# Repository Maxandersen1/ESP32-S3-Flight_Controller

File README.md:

# ESP32-S3 Custom Flight Controller

A custom-designed drone flight controller built from the ground up around the ESP32-S3 microcontroller. This project is a work-in-progress, covering everything from custom PCB design in KiCad to low-level sensor drivers and Web Serial 3D visualization.

## Hardware Features
- **Microcontroller**: ESP32-S3-WROOM-1 (Dual-Core Xtensa LX7, 240MHz)
- **IMU**: Bosch BMI088 (6-axis accelerometer & gyroscope) via SPI
- **Barometer**: Bosch BMP388 via I2C
- **Power System**: Onboard TPS54331 buck converter (battery Vin to 5V) & AMS1117-3.3 LDO
- **PCB**: Custom 4-layer PCB designed in KiCad, hand-soldered SMD components.

## Assembled PCB

## Hardware Design Process

### 1. Schematic
The schematic was designed in KiCad and ordered as a 4-layer PCB from JLCPCB.

### 2. PCB Layout & Stackup
The layout was routed in KiCad with the following dedicated 4-layer stackup:
* **Layer 1 – Top Layer (F.Cu):** Primary signal layer used for component placement (ESP32-S3, IMU, Barometer) and high-speed SPI/I2C trace routing.
* **Layer 2 – Inner Layer 1 (In1.Cu):** Dedicated internal Ground Plane (GND) providing low-impedance return paths and EMI shielding for sensitive sensors.
* **Layer 3 – Inner Layer 2 (In2.Cu):** Dedicated Power Plane with split power zones distributing clean 3.3V and 5V power across the board.
* **Layer 4 – Bottom Layer (B.Cu):** Secondary signal and ground layer used for remaining routing and bottom-side thermal dissipation.

## Bill of Materials (BOM)

### Integrated Circuits & Active Components
| Designator | Component / Part | Package | Qty | Function |
| :--- | :--- | :--- | :--- | :--- |
| **U1** | ESP32-S3-WROOM-1 | SMD Module | 1 | Main Flight Controller MCU |
| **U3** | Bosch BMI088 | LGA-16 | 1 | 6-Axis IMU (SPI) |
| **U4** | Bosch BMP388 | LGA-10 | 1 | Barometric Pressure & Altitude Sensor (I2C) |
| **U5** | TI TPS54331DG4 | SOIC-8 | 1 | Step-Down Buck Converter (Battery Vin to 5V) |
| **U6** | AMS1117-3.3 | SOT-223 | 1 | Low-Dropout (LDO) Linear Voltage Regulator (3.3V) |
| **U2** | USBLC6-2SC6 | SOT-23-6 | 1 | Low-Capacitance ESD Protection Array (USB) |
| **D1, D2, D3** | SS14 / SS34 | SMA (DO-214AC) | 3 | Schottky Barrier Diodes |
| **L1** | 15 µH (e.g. LVS606020) | SMD (~6x6 mm) | 1 | Power Inductor for Buck Converter |

### Connectors & Switches
| Designator | Description | Qty | Function |
| :--- | :--- | :--- | :--- |
| **J1** | USB-C 12-pin (TYPE-C-31-M-12) | 1 | USB Data / Programming & 5V Power |
| **J3** | JST-SH 8-Pin SMD (SM08B-SRSS-TB) | 1 | 4-in-1 ESC Interconnect (PWM / DSHOT signals) |
| **J2, J4** | 2.54mm Pitch Pin Headers | 2 | RC Receiver (UART) & Expansion / Debug pins |
| **SW1, SW2** | SMD Tactile Push Buttons | 2 | Bootloader & Hardware Reset |

### Passives Summary
* **Capacitors:**
  * `100 nF (0603)` — **8 pcs** (Decoupling for MCU, sensors, and regulators)
  * `10 nF (0603)` — **2 pcs** (Noise filtering / compensation)
  * `3.3 nF (0603)` — **1 pc** (Buck converter compensation loop)
  * `4.7 µF (0603)` — **1 pc** (Bulk decoupling)
  * `10 µF (0805)` — **1 pc** (LDO input/output stabilization)
  * `22 µF (0805)` — **4 pcs** (High-capacitance power rail smoothing)
* **Resistors (all 0603):**
  * `10 kΩ` — **7 pcs** (Pull-ups & boot mode configuration)
  * `4.7 kΩ` — **2 pcs** (I2C bus pull-ups for SDA / SCL)
  * `5.1 kΩ` — **2 pcs** (USB-C CC line pull-downs for 5V power negotiation)
  * `100 kΩ` — **2 pcs** (Voltage dividers & enable lines)
  * `30 kΩ` — **1 pc** (Feedback network)
  * `52.3 kΩ` — **1 pc** (High-precision feedback resistor for buck regulator)

## Software / Firmware
The firmware is written in C++ (Arduino framework) and features:
- **Raw SPI Communication**: Bypasses bloated libraries to communicate directly with the BMI088 registers, resolving complex ESP32 HAL macro conflicts.
- **Sensor Fusion**: Implements a custom Complementary Filter combining high-speed gyro data with accelerometer gravity vectors for stable, drift-free Pitch and Roll calculation.
- **Barometric Altimeter**: Features an auto-zeroing routine on startup to establish local ground-level pressure before calculating relative altitude in meters.

## 3D Web Visualizer
Included in the `tools/` directory is a custom HTML5/Three.js 3D drone visualizer. 
It uses the modern **Web Serial API** to connect directly to the flight controller via USB (no servers required) and renders the drone's orientation in real-time at 60fps based on the live IMU telemetry.

## Directory Structure
- `hardware/`: KiCad schematics and PCB layout files.
- `firmware/FlightController/`: The main C++ Arduino sketch containing sensor drivers and mathematical filters.
- `tools/`: Contains `3D_Viewer.html` (Double-click to open in a modern browser).

## Roadmap / To-Do
- [x] PCB Design & Assembly
- [x] I2C & SPI Bring-up
- [x] Raw IMU & Barometer Data Extraction
- [x] Sensor Fusion (Complementary Filter)
- [x] Real-time 3D Visualization
- [ ] PID Controller Implementation
- [ ] ESC Motor Output (DSHOT/PWM)
- [ ] Radio Receiver Integration (ExpressLRS/Crossfire)

*Hardware designed from scratch by Max. Firmware and 3D visualization developed using AI-assisted pair programming.*

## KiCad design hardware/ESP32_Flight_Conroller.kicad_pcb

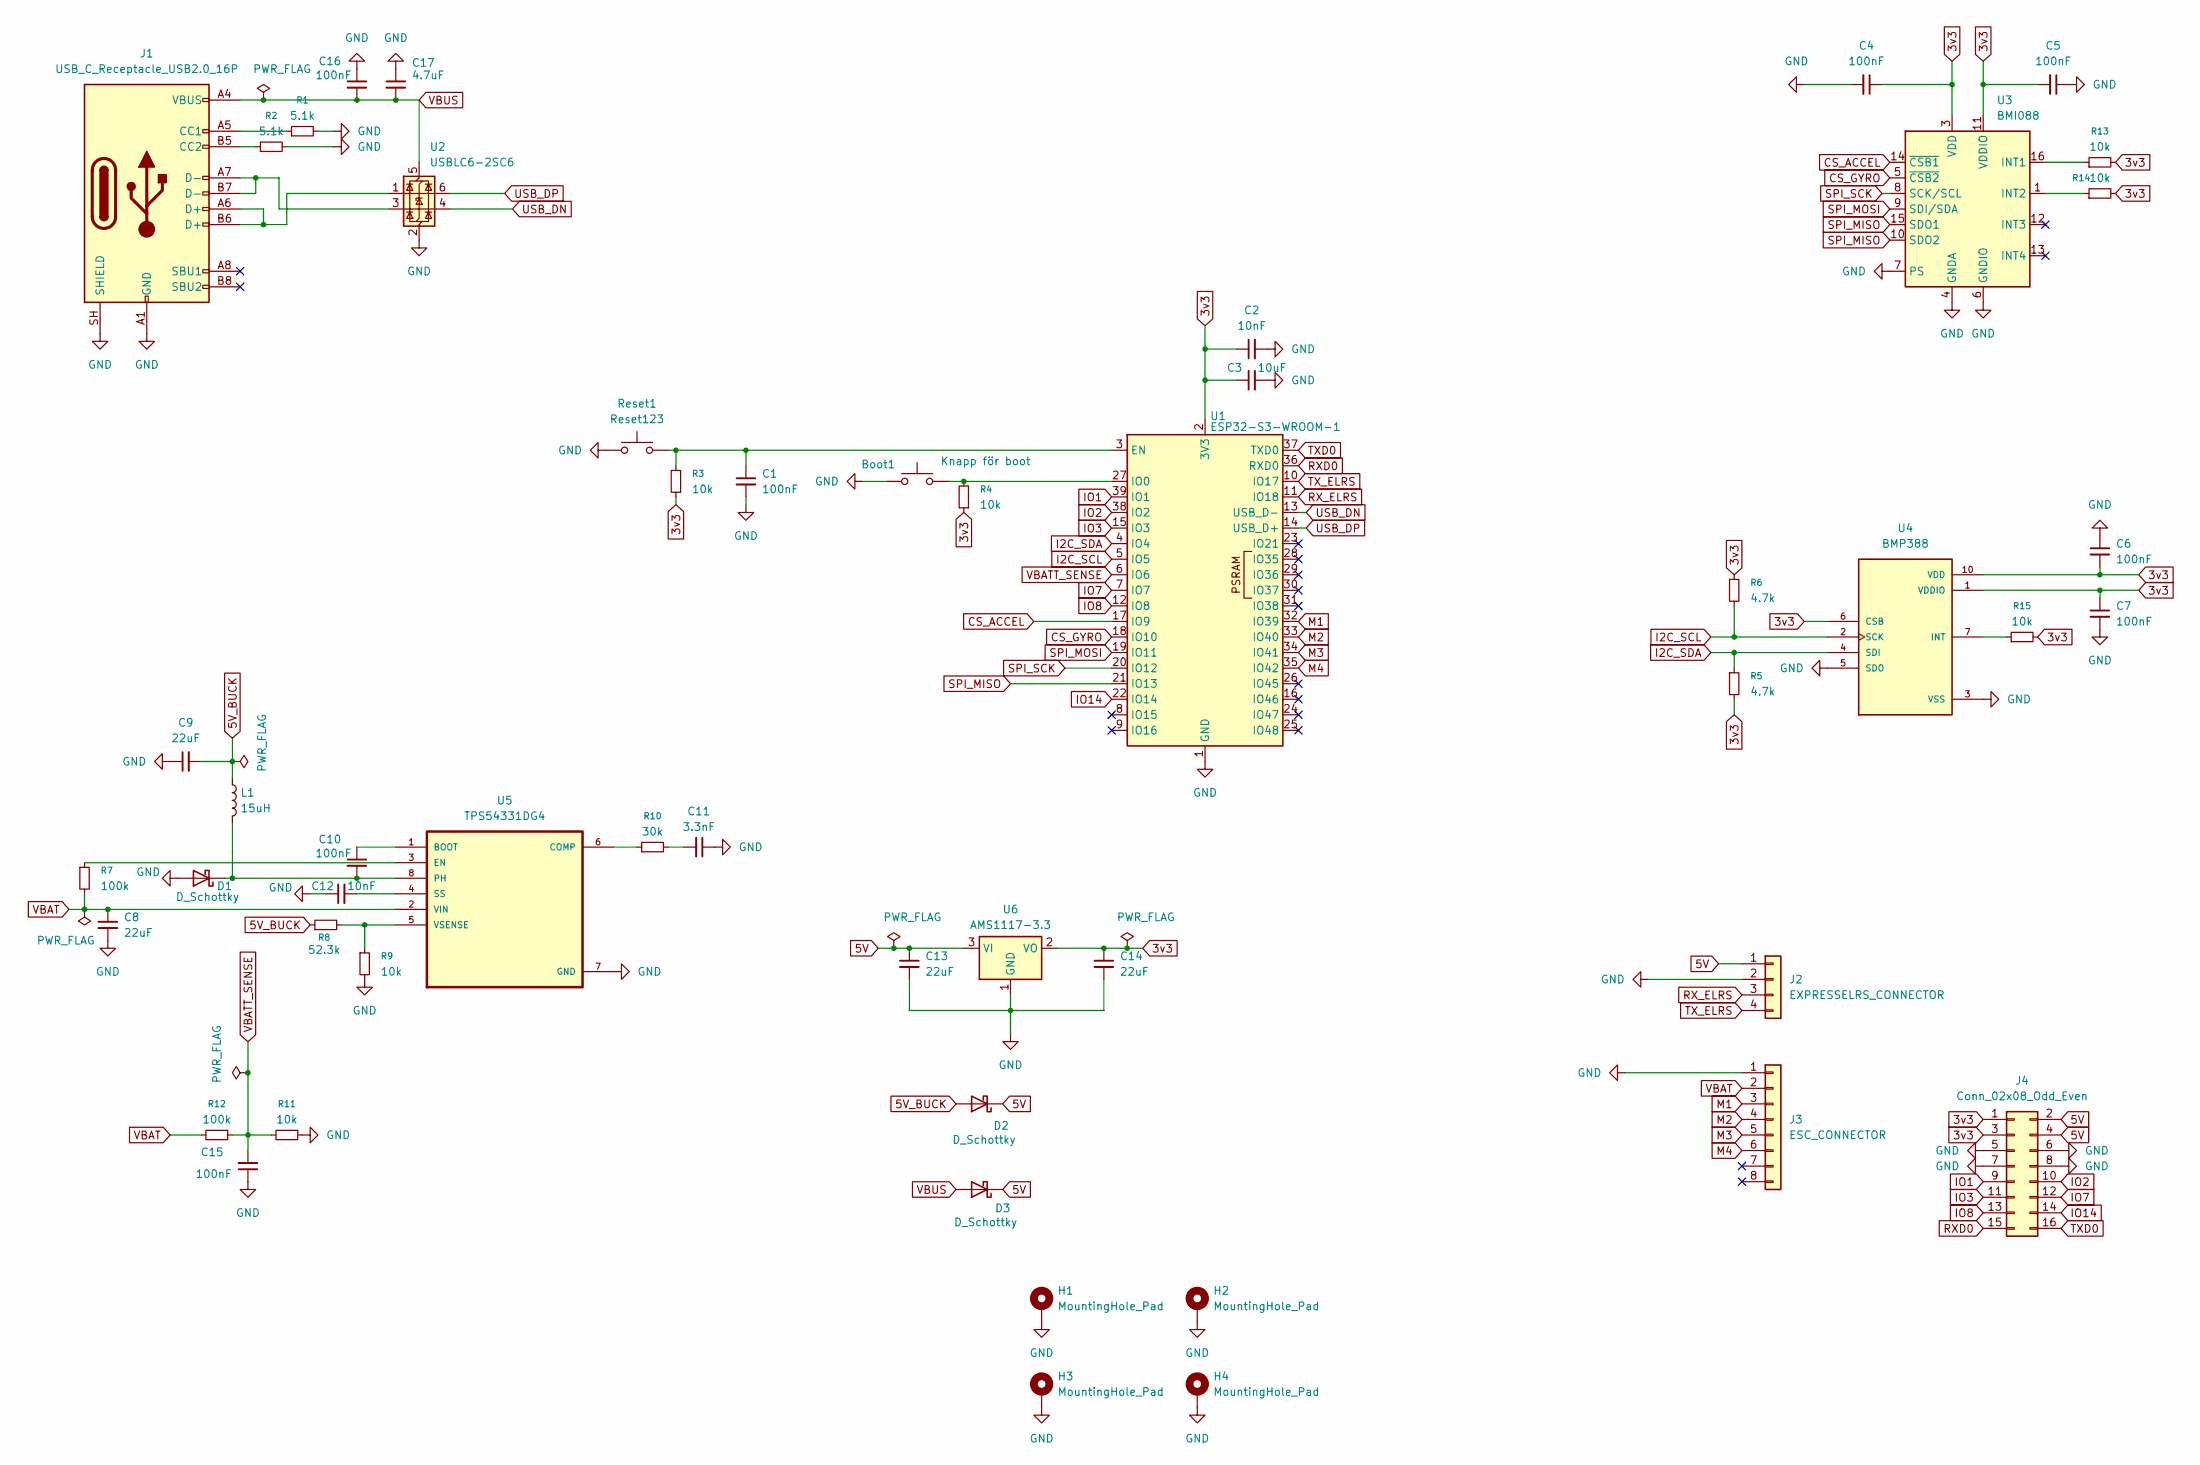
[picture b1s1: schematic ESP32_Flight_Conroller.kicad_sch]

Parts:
Boot1: Knapp för boot; SW_SPST_B3U-1000P
C1, C4, C5, C6, C7, C10, C15, C16: 100nF; C_0603_1608Metric_Pad1.08x0.95mm_HandSolder
C2, C12: 10nF; C_0603_1608Metric_Pad1.08x0.95mm_HandSolder
C3: 10uF; C_0805_2012Metric_Pad1.18x1.45mm_HandSolder
C8, C9, C13, C14: 22uF; C_0805_2012Metric_Pad1.18x1.45mm_HandSolder
C11: 3.3nF; C_0603_1608Metric_Pad1.08x0.95mm_HandSolder
C17: 4.7uF; C_0603_1608Metric_Pad1.08x0.95mm_HandSolder
D1, D2, D3: D_Schottky; D_SMA
H1, H2, H3, H4: MountingHole_Pad; MountingHole_3mm_Pad
J1: USB_C_Receptacle_USB2.0_16P; USB_C_Receptacle_HRO_TYPE-C-31-M-12
J2: EXPRESSELRS_CONNECTOR; PinHeader_1x04_P2.54mm_Vertical
J3: ESC_CONNECTOR; JST_SH_SM08B-SRSS-TB_1x08-1MP_P1.00mm_Horizontal
J4: Conn_02x08_Odd_Even; PinHeader_2x08_P2.54mm_Vertical
L1: 15uH; L_6.3x6.3_H3
R1, R2: 5.1k; R_0603_1608Metric_Pad0.98x0.95mm_HandSolder
R3, R4, R9, R11, R13, R14, R15: 10k; R_0603_1608Metric_Pad0.98x0.95mm_HandSolder
R5, R6: 4.7k; R_0603_1608Metric_Pad0.98x0.95mm_HandSolder
R7, R12: 100k; R_0603_1608Metric_Pad0.98x0.95mm_HandSolder
R8: 52.3k; R_0603_1608Metric_Pad0.98x0.95mm_HandSolder
R10: 30k; R_0603_1608Metric_Pad0.98x0.95mm_HandSolder
Reset1: Reset123; SW_SPST_B3U-1000P
U1: ESP32-S3-WROOM-1; ESP32-S3-WROOM-1U
U2: USBLC6-2SC6; SOT-23-6
U3: BMI088; Bosch_LGA-16_4.5x3mm_P0.5mm_LayoutBorder7x1y_ClockwisePinNu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
U4: BMP388; XDCR_BMP388; PARTREV 1.7
U5: TPS54331DG4; SOIC-8_3.9x4.9mm_P1.27mm
U6: AMS1117-3.3; SOT-223-3_TabPin2

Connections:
3v3: C2.1, C3.1, C4.1, C5.2, C6.2, C7.1, C14.1, J4.1, J4.3, R3.1, R4.1, R5.2, R6.1, R13.2, R14.2, R15.2, U1.2 (3V3), U3.3 (VDD), U3.11 (VDDIO), U4.1 (VDDIO), U4.6 (CSB), U4.10 (VDD), U6.2 (VO)
5V: C13.1, D2.1 (K), D3.1 (K), J2.1, J4.2, J4.4, U6.3 (VI)
5V_BUCK: C9.2, D2.2 (A), L1.1, R8.1
CS_ACCEL: U1.17 (IO9), U3.14 (~CSB1)
CS_GYRO: U1.18 (IO10), U3.5 (~CSB2)
GND: Boot1.1, C1.2, C2.2, C3.2, C4.2, C5.1, C6.1, C7.2, C8.2, C9.1, C11.1, C12.1, C13.2, C14.2, C15.1, C16.1, C17.1, D1.2 (A), H1.1 (1_1), H2.1 (1_1), H3.1 (1_1), H4.1 (1_1), J1.A1 (GND), J1.A12 (GND), J1.B1 (GND), J1.B12 (GND), J1.SH (SHIELD), J2.2, J3.1, J4.5, J4.6, J4.7, J4.8, R1.2, R2.2, R9.2, R11.1, Reset1.1, U1.1 (GND), U1.40 (GND), U1.41 (GND), U2.2 (GND), U3.2 (GNDA), U3.4 (GNDA), U3.6 (GNDIO), U3.7 (PS), U4.3 (VSS), U4.5 (SDO), U4.8 (VSS), U4.9 (VSS), U5.7 (GND), U6.1 (GND)
I2C_SCL: R6.2, U1.5 (IO5), U4.2 (SCK)
I2C_SDA: R5.1, U1.4 (IO4), U4.4 (SDI)
IO1: J4.9, U1.39 (IO1)
IO2: J4.10, U1.38 (IO2)
IO3: J4.11, U1.15 (IO3)
IO7: J4.12, U1.7 (IO7)
IO8: J4.13, U1.12 (IO8)
IO14: J4.14, U1.22 (IO14)
M1: J3.3, U1.32 (IO39)
M2: J3.4, U1.33 (IO40)
M3: J3.5, U1.34 (IO41)
M4: J3.6, U1.35 (IO42)
unnamed: C11.2, R10.2
unnamed: C10.2, D1.1 (K), L1.2, U5.8 (PH)
unnamed: J1.A5 (CC1), R1.1
unnamed: J1.B5 (CC2), R2.1
unnamed: J1.A6 (D+), J1.B6 (D+), U2.1 (I/O1)
unnamed: J1.A7 (D-), J1.B7 (D-), U2.3 (I/O2)
unnamed: C1.1, R3.2, Reset1.2, U1.3 (EN)
unnamed: Boot1.2, R4.2, U1.27 (IO0)
unnamed: R13.1, U3.16 (INT1)
unnamed: R14.1, U3.1 (INT2)
unnamed: R15.1, U4.7 (INT)
unnamed: C10.1, U5.1 (BOOT)
unnamed: R10.1, U5.6 (COMP)
unnamed: R7.1, U5.3 (EN)
unnamed: C12.2, U5.4 (SS)
unnamed: R8.2, R9.1, U5.5 (VSENSE)
RXD0: J4.15, U1.36 (RXD0)
RX_ELRS: J2.3, U1.11 (IO18)
SPI_MISO: U1.21 (IO13), U3.10 (SDO2), U3.15 (SDO1)
SPI_MOSI: U1.19 (IO11), U3.9 (SDI/SDA)
SPI_SCK: U1.20 (IO12), U3.8 (SCK/SCL)
TXD0: J4.16, U1.37 (TXD0)
TX_ELRS: J2.4, U1.10 (IO17)
USB_DN: U1.13 (USB_D-), U2.4 (I/O2)
USB_DP: U1.14 (USB_D+), U2.6 (I/O1)
VBAT: C8.1, J3.2, R7.2, R12.2, U5.2 (VIN)
VBATT_SENSE: C15.2, R11.2, R12.1, U1.6 (IO6)
VBUS: C16.2, C17.2, D3.2 (A), J1.A4 (VBUS), J1.A9 (VBUS), J1.B4 (VBUS), J1.B9 (VBUS), U2.5 (VBUS)

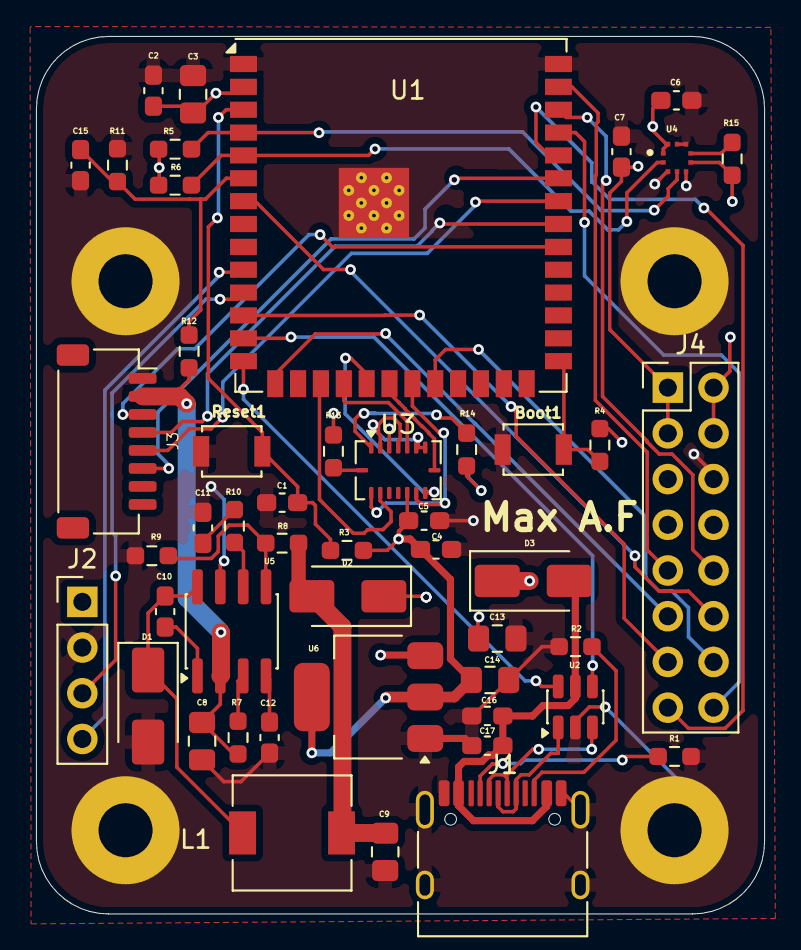
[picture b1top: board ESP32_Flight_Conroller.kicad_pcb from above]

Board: 4 copper layers, 40.5 x 48.8 mm, 52 parts (0 on the bottom side), 46 nets.

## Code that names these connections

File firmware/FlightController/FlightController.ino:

#include <SPI.h>
#include <Wire.h>
#include <math.h>
#include <Adafruit_Sensor.h>
#include "Adafruit_BMP3XX.h"

// --- PINS ---
#define I2C_SDA 4
#define I2C_SCL 5
#define SPI_MOSI 11
#define SPI_MISO 13
#define SPI_SCK  12
#define CS_ACCEL 9
#define CS_GYRO  10

Adafruit_BMP3XX bmp;

void writeSPI(int cs_pin, byte reg, byte value) {
  SPI.beginTransaction(SPISettings(1000000, MSBFIRST, SPI_MODE0));
  digitalWrite(cs_pin, LOW);
  SPI.transfer(reg); 
  SPI.transfer(value);
  digitalWrite(cs_pin, HIGH);
  SPI.endTransaction();
}

float pitch = 0;
float roll = 0;
unsigned long last_time = 0;

float baseline_pressure = 1013.25; 
float current_altitude = 0.0;

void setup() {
  Serial.begin(115200);
  delay(1000);
  
  // Start I2C and Barometer
  Wire.begin(I2C_SDA, I2C_SCL);
  if (bmp.begin_I2C(0x76, &Wire)) {
    bmp.setTemperatureOversampling(BMP3_OVERSAMPLING_8X);
    bmp.setPressureOversampling(BMP3_OVERSAMPLING_4X);
    bmp.setIIRFilterCoeff(BMP3_IIR_FILTER_COEFF_3);
    bmp.setOutputDataRate(BMP3_ODR_50_HZ);

    for(int i=0; i<10; i++) {
       bmp.performReading();
       delay(20);
    }

    float sum_pressure = 0;
    for(int i=0; i<50; i++) {
       bmp.performReading();
       sum_pressure += (bmp.pressure / 100.0); 
       delay(20);
    }
    baseline_pressure = sum_pressure / 50.0;
  }

  // Start IMU
  pinMode(CS_ACCEL, OUTPUT);
  pinMode(CS_GYRO, OUTPUT);
  digitalWrite(CS_ACCEL, HIGH);
  digitalWrite(CS_GYRO, HIGH);
  SPI.begin(SPI_SCK, SPI_MISO, SPI_MOSI, -1);

  writeSPI(CS_ACCEL, 0x7F, 0x00);
  delay(10);
  writeSPI(CS_ACCEL, 0x7D, 0x04);
  delay(50);
  writeSPI(CS_ACCEL, 0x7C, 0x00);
  delay(50);

  last_time = micros();
}

void loop() {
  SPI.beginTransaction(SPISettings(1000000, MSBFIRST, SPI_MODE0));

  // --- LÄS ACCEL ---
  digitalWrite(CS_ACCEL, LOW);
  SPI.transfer(0x12 | 0x80); 
  SPI.transfer(0x00);        
  byte ax_l = SPI.transfer(0x00); byte ax_h = SPI.transfer(0x00);
  byte ay_l = SPI.transfer(0x00); byte ay_h = SPI.transfer(0x00);
  byte az_l = SPI.transfer(0x00); byte az_h = SPI.transfer(0x00);
  digitalWrite(CS_ACCEL, HIGH);

  float acc_x = ((int16_t)((ax_h << 8) | ax_l)) / 10922.0f;
  float acc_y = ((int16_t)((ay_h << 8) | ay_l)) / 10922.0f;
  float acc_z = ((int16_t)((az_h << 8) | az_l)) / 10922.0f;

  // --- LÄS GYRO ---
  digitalWrite(CS_GYRO, LOW);
  SPI.transfer(0x02 | 0x80);
  byte gx_l = SPI.transfer(0x00); byte gx_h = SPI.transfer(0x00);
  byte gy_l = SPI.transfer(0x00); byte gy_h = SPI.transfer(0x00);
  byte gz_l = SPI.transfer(0x00); byte gz_h = SPI.transfer(0x00);
  digitalWrite(CS_GYRO, HIGH);

  float gyr_x = ((int16_t)((gx_h << 8) | gx_l)) / 16.384f;
  float gyr_y = ((int16_t)((gy_h << 8) | gy_l)) / 16.384f;
  float gyr_z = ((int16_t)((gz_h << 8) | gz_l)) / 16.384f;

  SPI.endTransaction();

  // --- Complementary Filter ---
  unsigned long now = micros();
  float dt = (now - last_time) / 1000000.0f; 
  last_time = now;

  float pitch_acc = atan2(acc_x, sqrt(acc_y*acc_y + acc_z*acc_z)) * 180.0 / PI;
  float roll_acc  = atan2(acc_y, sqrt(acc_x*acc_x + acc_z*acc_z)) * 180.0 / PI;

  pitch = 0.98 * (pitch - gyr_y * dt) + 0.02 * pitch_acc;
  roll  = 0.98 * (roll  + gyr_x * dt) + 0.02 * roll_acc;

  // --- LÄS BAROMETERN ---
  if (bmp.performReading()) {
      current_altitude = bmp.readAltitude(baseline_pressure);
  }

  // Serial output for 3D Viewer
  Serial.print(pitch);
  Serial.print(",");
  Serial.print(roll);
  Serial.print(",");
  Serial.println(current_altitude);
  
  delay(10); 
}
